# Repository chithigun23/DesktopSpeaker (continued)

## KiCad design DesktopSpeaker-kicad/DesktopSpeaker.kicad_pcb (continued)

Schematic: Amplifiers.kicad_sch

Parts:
C260, C267, C276, C278, C281, C289, C291, C294, C314: 100nF; C_0402_1005Metric_Pad0.74x0.62mm_HandSolder; MPN GRM155R71H104KE14D; LCSC C77020
C261, C262, C263, C264: 22uF 10V; C_0805_2012Metric_Pad1.18x1.45mm_HandSolder; MPN GRM21BZ71A226ME15L; LCSC C907991
C265: 2.2uF; C_0805_2012Metric_Pad1.18x1.45mm_HandSolder; MPN CL21B225KAFNNNE; LCSC C19110
C266: 47nF; C_0402_1005Metric_Pad0.74x0.62mm_HandSolder; MPN GRM155R71H473KE14D; LCSC C117757
C268: 6.8nF; C_0402_1005Metric_Pad0.74x0.62mm_HandSolder; MPN CL05B682KB5NNNC; LCSC C318580
C269: 47pF; C_0402_1005Metric_Pad0.74x0.62mm_HandSolder; MPN GRM1555C1H470JA01D; LCSC C76970
C270: 1uF; C_0805_2012Metric_Pad1.18x1.45mm_HandSolder; MPN CL21B105KBFNNNE; LCSC C28323
C271, C272, C273, C274, C277, C279, C290, C292: 22uF 25V; C_0805_2012Metric_Pad1.18x1.45mm_HandSolder; MPN CL21A226MAQNNNE; LCSC C45783
C275: 100uF 25V; CP_Elec_8x10; MPN EEHZA1E101XP; LCSC C264047
C280, C293: 4.7uF; C_0805_2012Metric_Pad1.18x1.45mm_HandSolder; MPN CL21A475KAQNNNE; LCSC C1779
C282, C283, C284, C295, C296, C297: 1uF; C_0402_1005Metric_Pad0.74x0.62mm_HandSolder; MPN CL05A105KO5NNNC; LCSC C29266
C285, C286, C287, C288, C298, C299, C300, C301: 0.47uF; C_0402_1005Metric_Pad0.74x0.62mm_HandSolder; MPN CGA0402X7R474K160GT; LCSC C22435970
C302, C303, C304, C305, C306, C307: 0.68uF 50V; C_0805_2012Metric_Pad1.18x1.45mm_HandSolder; MPN CL21B684KBFVPNE; LCSC C472832
J9, J10, J11: B2P-VH; JST_B2P_VH_1x02_P3.96mm_Vertical; MPN B2P-VH(LF)(SN); LCSC Part C160315
L200: 2.2uH; L_Coilcraft_XAL7070-XXX; MPN XAL7070-222MEC; LCSC C3911470
L201, L202, L203, L204, L205, L206: 22uH; L_Sunlord_MWSA1265S; MPN MWSA1265S-220MT; LCSC C7245133
R250: 499k; R_0402_1005Metric_Pad0.72x0.64mm_HandSolder; MPN RC0402FR-07499KL; LCSC C137971
R251: 56k; R_0402_1005Metric_Pad0.72x0.64mm_HandSolder; MPN RC0402FR-0756KL; LCSC C114756
R252: 301k; R_0402_1005Metric_Pad0.72x0.64mm_HandSolder; MPN RC0402FR-07301KL; LCSC C171693
R253: 150k; R_0402_1005Metric_Pad0.72x0.64mm_HandSolder; MPN RC0402FR-07150KL; LCSC C93947
R254: 82k; R_0402_1005Metric_Pad0.72x0.64mm_HandSolder; MPN AC0402FR-0782KL; LCSC C144735
R255, R259: 100k; R_0402_1005Metric_Pad0.72x0.64mm_HandSolder; MPN RC0402FR-07100KL; LCSC C60491
R256: 0R DNP; R_0402_1005Metric_Pad0.72x0.64mm_HandSolder; MPN RC0402FR-070RL; LCSC C106231; not fitted
R257, R258, R261: 1k; R_0402_1005Metric_Pad0.72x0.64mm_HandSolder; MPN RC0402FR-071KL; LCSC C106235
R262: 10k; R_0402_1005Metric_Pad0.72x0.64mm_HandSolder; MPN RC0402FR-0710KL; LCSC C60490
TP10: PVDD_AMP; TestPoint_Keystone_5015_Micro_Mini
TP20: AMP_FAULT_N; TestPoint_Keystone_5015_Micro_Mini
TP24: GND; TestPoint_Keystone_5010-5014_Multipurpose
U6, U7: TAS5825MRHBR; MPN TAS5825MRHBR; LCSC Part C471049
U25: TPS61088RHLR; MPN TPS61088RHLR; LCSC Part C87357

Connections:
/3V3_AUDIO: C280.1, C281.1, C293.1, C294.1, R262.1, U6.6 (DVDD), U7.6 (DVDD); also elsewhere on the board
/AMP_BOOST_EN: R255.1, U25.2 (EN); also elsewhere on the board
/AMP_FAULT_N: R262.2, TP20.1, U6.9 (GPIO0), U7.9 (GPIO0); also elsewhere on the board
/AMP_PDN: R257.1, R258.1, R259.1; also elsewhere on the board
/AUD_SCL: U6.16 (SCL), U7.16 (SCL); also elsewhere on the board
/AUD_SDA: U6.15 (SDA), U7.15 (SDA); also elsewhere on the board
/Amplifiers/PVDD_AMP: C270.1, C271.1, C272.1, C273.1, C274.1, C275.1 (+), C276.1, C277.1, C278.1, C279.1, C289.1, C290.1, C291.1, C292.1, C314.1, R250.1, TP10.1, U6.3, U6.4, U6.21, U6.22, U6.[3,4,21,22] (PVDD), U7.3, U7.4, U7.21, U7.22, U7.[3,4,21,22] (PVDD), U25.14, U25.15, U25.16, U25.[14-16] (VOUT)
/I2S_BCK: U6.13 (SCLK), U7.13 (SCLK); also elsewhere on the board
/I2S_LRCK: U6.12 (LRCLK), U7.12 (LRCLK); also elsewhere on the board
/I2S_SDATA: U6.14 (SDIN), U7.14 (SDIN); also elsewhere on the board
/SYS_RAW: C260.1, C261.1, C262.1, C263.1, C264.1, L200.1, U25.9 (VIN); also elsewhere on the board
GND: C260.2, C261.2, C262.2, C263.2, C264.2, C265.2, C266.2, C268.2, C269.2, C270.2, C271.2, C272.2, C273.2, C274.2, C275.2 (-), C276.2, C277.2, C278.2, C279.2, C280.2, C281.2, C282.2, C283.2, C284.2, C289.2, C290.2, C291.2, C292.2, C293.2, C294.2, C295.2, C296.2, C297.2, C302.2, C303.2, C304.2, C305.2, C306.2, C307.2, C314.2, R251.2, R253.2, R255.2, R256.2, R259.2, R261.1, TP24.1, U6.5, U6.8 (ADR), U6.20, U6.25, U6.26, U6.31, U6.32, U6.33, U6.[5,20,25,26,31,32,3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 (GND), U7.5, U7.20, U7.25, U7.26, U7.31, U7.32, U7.33, U7.[5,20,25,26,31,32,3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 (GND), U25.11, U25.12, U25.20 (AGND), U25.21, U25.[11,12,21] (PGND); also elsewhere on the board
unnamed: C268.1, R254.2
unnamed: C302.1, J9.1, L201.2
unnamed: C303.1, J9.2, L202.2
unnamed: C304.1, J10.1, L203.2
unnamed: C305.1, J10.2, L204.2
unnamed: C306.1, J11.1, L205.2
unnamed: C307.1, J11.2, L206.2
unnamed: C284.1, U6.19 (AVDD)
unnamed: C285.1, U6.1 (BST_A+)
unnamed: C286.2, U6.29 (BST_A-)
unnamed: C287.1, U6.24 (BST_B+)
unnamed: C288.2, U6.28 (BST_B-)
unnamed: C283.1, U6.18 (GVDD)
unnamed: C285.2, L201.1, U6.2 (OUT_A+)
unnamed: C286.1, L202.1, U6.30 (OUT_A-)
unnamed: C287.2, L203.1, U6.23 (OUT_B+)
unnamed: C288.1, L204.1, U6.27 (OUT_B-)
unnamed: C282.1, U6.7 (VR_DIG)
unnamed: R257.2, U6.17 (~PDN)
unnamed: R261.2, U7.8 (ADR)
unnamed: C297.1, U7.19 (AVDD)
unnamed: C298.1, U7.1 (BST_A+)
unnamed: C299.2, U7.29 (BST_A-)
unnamed: C300.1, U7.24 (BST_B+)
unnamed: C301.2, U7.28 (BST_B-)
unnamed: C296.1, U7.18 (GVDD)
unnamed: C298.2, C299.1, L205.1, U7.2 (OUT_A+), U7.30 (OUT_A-)
unnamed: C300.2, C301.1, L206.1, U7.23 (OUT_B+), U7.27 (OUT_B-)
unnamed: C295.1, U7.7 (VR_DIG)
unnamed: R258.2, U7.17 (~PDN)
unnamed: C267.1, U25.8 (BOOT)
unnamed: C269.1, R254.1, U25.18 (COMP)
unnamed: R250.2, R251.1, U25.17 (FB)
unnamed: R252.1, U25.3 (FSW)
unnamed: R253.1, U25.19 (ILIM)
unnamed: R256.1, U25.13 (MODE)
unnamed: C266.1, U25.10 (SS)
unnamed: C267.2, L200.2, R252.2, U25.4, U25.5, U25.6, U25.7, U25.[4-7] (SW)
unnamed: C265.1, U25.1 (VCC)

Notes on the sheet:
FRONT_L
FRONT_R
WOOFER
U7 PBTL pairing verified against SLASEH7F Fig. 159 / 10.2.5 (page 86 rendered): OUT_A+ (2) with OUT_A- (30) merged to L205; OUT_B+ (23) with OUT_B- (27) merged to L206; speaker between the two filtered nodes.
Firmware: write DAMP_PBTL (reg 0x02 bit 2) = 1 on U7 before it leaves Hi-Z; the PBTL mixer takes the left I2S frame, so the U7 DSP forms (L+R)/2. No cycle-by-cycle current limit in PBTL.
U25: VOUT = 1.204 V x (1 + 499k/56k) = 11.93 V (PFM: 12.0 V; OVP 12.7-13.6 V). FSW about 494 kHz (RFREQ 301k). ILIM 150k = 7.9 A typ, 6.6 A min in PFM (equation 3). L200 Isat 19.6 A.
COMP: R254 82k, C268 6.8nF, C269 47pF (equations 18-20, fc about 5 kHz, effective Co about 170 uF): calculated only, bench check required. MODE floating = PFM; R256 DNP 0R to GND = forced PWM.
TAS5825M addresses: U6 ADR tied directly to GND = 0x4C, U7 ADR 1k = 0x4D. AMP_PDN shared (1k each, 100k pull-down). GPIO0 = FAULTZ (open drain) wired-OR to AMP_FAULT_N, 10k pull-up to 3V3_AUDIO. GPIO1/2 not connected.
DVDD = 3V3_AUDIO. Bootstrap caps are 0.47uF (Table 66). Filter 22uH + 0.68uF per output. No MCLK pin: TAS5825M locks to SCLK. Speaker connectors: pin 1 +, pin 2 -.

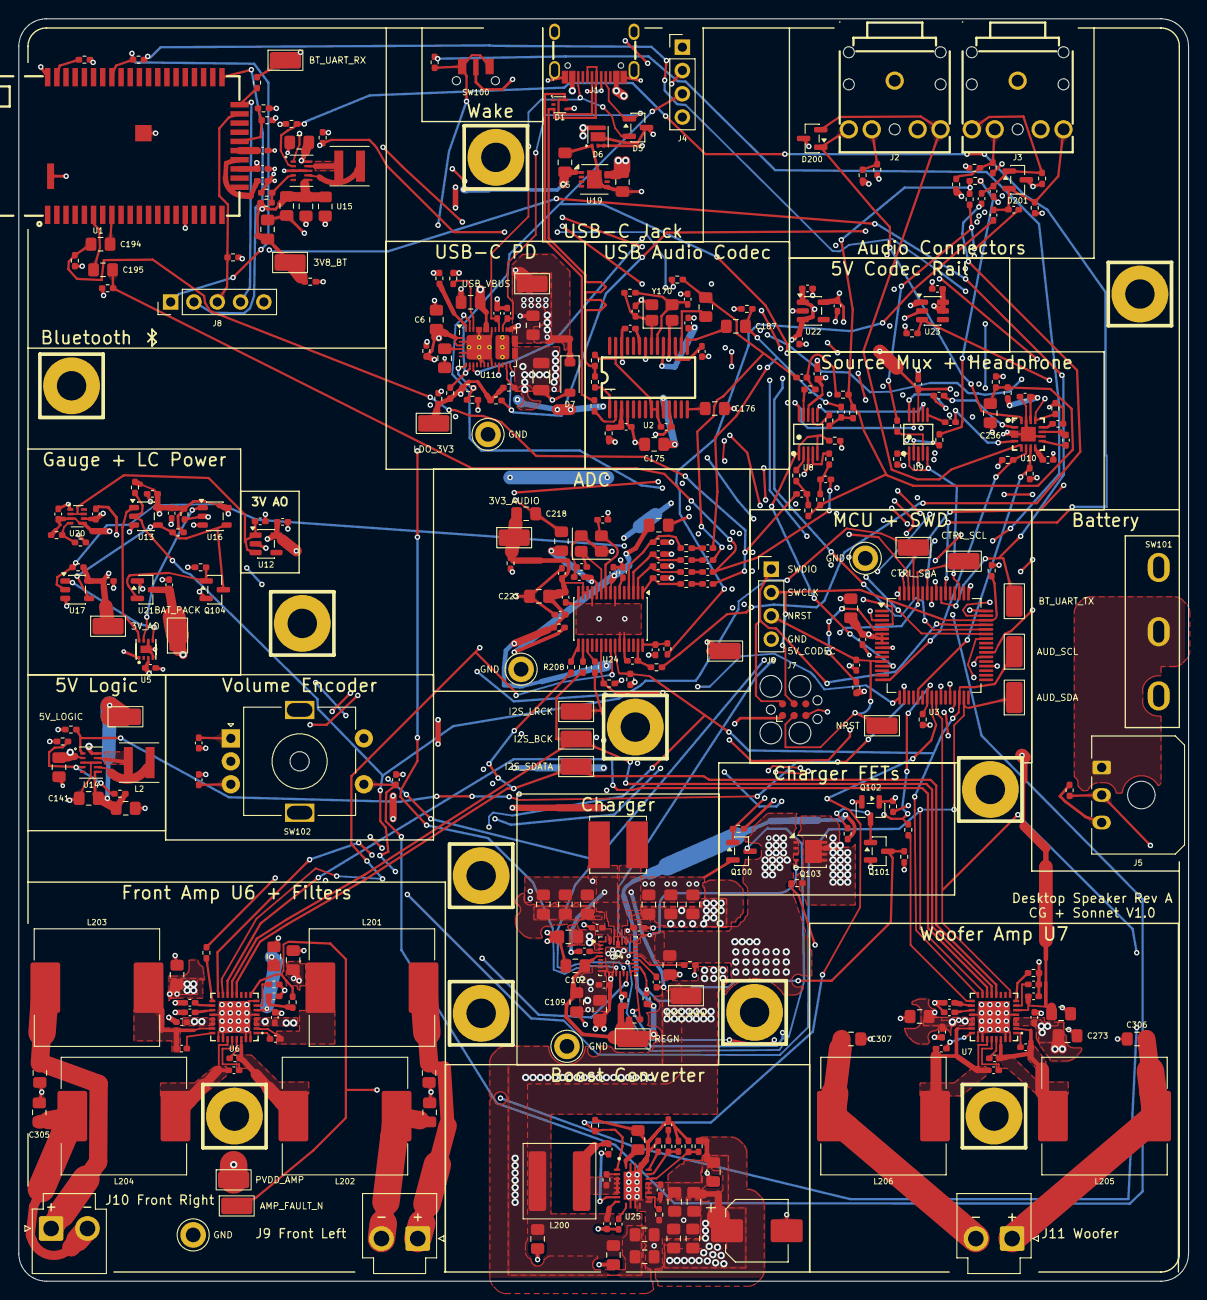
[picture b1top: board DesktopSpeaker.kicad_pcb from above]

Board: 4 copper layers, 127.5 x 137.6 mm, 360 parts (1 on the bottom side), 208 nets.

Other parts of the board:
H1, H2, H3, H4, H5, H6, H7, H8, H9: M3 PTH GND; MountingHole_3.2mm_M3_PTH_GND
HA1, HA2: M3 PTH GND; MountingHole_3.2mm_M3_PTH_GND
LOGO1: Orwellian Industries; Logo_Orwellian

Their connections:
GND: H1.1, H2.1, H3.1, H4.1, H5.1, H6.1, H7.1, H8.1, H9.1, HA1.1, HA2.1; also elsewhere on the board

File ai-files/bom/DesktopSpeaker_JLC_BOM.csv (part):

Comment,Designator,Footprint,LCSC Part #,MPN,Manufacturer,Qty
4.7uF X7R 50V,"C2,C5",C_0805_2012Metric_Pad1.18x1.45mm_HandSolder,C5159426,C2012X7R1H475KT0A0E,TDK,2
22uF 10V X7R,"C6,C104,C105,C106,C107,C140,C141,C142,C150,C152,C153,C154,C261,C262,C263,C264",C_0805_2012Metric_Pad1.18x1.45mm_HandSolder,C907991,GRM21BZ71A226ME15L,Murata,16
10uF / 50V,"C100,C101,C108,C111,C112",C_0805_2012Metric_Pad1.18x1.45mm_HandSolder,C440198,GRM21BR61H106KE43L,Murata,5
10uF,"C102,C109,C175,C176,C181,C190,C214,C216,C218,C223",C_0805_2012Metric_Pad1.18x1.45mm_HandSolder,C32635,CL21B106KPQNNNE,Samsung Electro-Mechanics,10
47nF / 50V,"C103,C110,C266",C_0402_1005Metric_Pad0.74x0.62mm_HandSolder,C117757,GRM155R71H473KE14D,Murata,3
100nF,"C120,C126,C130,C131,C132,C160,C162,C191,C213,C215,C217,C219,C237,C238,C246,C260,C267,C276,C278,C281,C289,C291,C294,C311,C312,C313,C314",C_0402_1005Metric_Pad0.74x0.62mm_HandSolder,C77020,GRM155R71H104KE14D,Murata,27
1uF,"C122,C123,C124,C125,C170,C171,C172,C173,C174,C192,C193,C212,C220,C221,C222,C224,C225,C230,C231,C232,C233,C234,C235,C239,C240,C245,C282,C283,C284,C295,C296,C297",C_0402_1005Metric_Pad0.74x0.62mm_HandSolder,C29266,CL05A105KO5NNNC,Samsung Electro-Mechanics,32
4.7uF,"C161,C186,C187,C194,C195,C236,C280,C293",C_0805_2012Metric_Pad1.18x1.45mm_HandSolder,C1779,CL21A475KAQNNNE,Samsung Electro-Mechanics,8
33pF,"C177,C178",C_0402_1005Metric_Pad0.74x0.62mm_HandSolder,C5137486,FCC0402N330J500AT,FOJAN,2
330pF C0G CC1 filter,"C182,C183",C_0402_1005Metric_Pad0.74x0.62mm_HandSolder,C76965,GRM1555C1H331JA01D,Murata,2
1uF X7R 50V,"C184,C270,C316",C_0805_2012Metric_Pad1.18x1.45mm_HandSolder,C28323,CL21B105KBFNNNE,Samsung Electro-Mechanics,3
2.2uF,"C200,C201,C202,C203,C204,C205,C241,C243,C244",C_0402_1005Metric_Pad0.74x0.62mm_HandSolder,C7464343,CL05A225KP5NNNC,Samsung Electro-Mechanics,9
10nF C0G,"C206,C207,C208,C209,C210,C211",C_0402_1005Metric_Pad0.74x0.62mm_HandSolder,C22400107,GRM1555C1H103JE01D,Murata,6
15pF C0G,"C226,C227",C_0402_1005Metric_Pad0.74x0.62mm_HandSolder,C76950,GRM1555C1H150JA01D,Murata,2
2.2uF,C265,C_0805_2012Metric_Pad1.18x1.45mm_HandSolder,C19110,CL21B225KAFNNNE,Samsung Electro-Mechanics,1
6.8nF,C268,C_0402_1005Metric_Pad0.74x0.62mm_HandSolder,C318580,CL05B682KB5NNNC,Samsung Electro-Mechanics,1
47pF,C269,C_0402_1005Metric_Pad0.74x0.62mm_HandSolder,C76970,GRM1555C1H470JA01D,Murata,1
22uF 25V,"C271,C272,C273,C274,C277,C279,C290,C292",C_0805_2012Metric_Pad1.18x1.45mm_HandSolder,C45783,CL21A226MAQNNNE,Samsung Electro-Mechanics,8
100uF 25V,C275,CP_Elec_8x10,C264047,EEHZA1E101XP,Panasonic,1
0.47uF,"C285,C286,C287,C288,C298,C299,C300,C301",C_0402_1005Metric_Pad0.74x0.62mm_HandSolder,C22435970,CGA0402X7R474K160GT,HRE,8
0.68uF 50V,"C302,C303,C304,C305,C306,C307",C_0805_2012Metric_Pad1.18x1.45mm_HandSolder,C472832,CL21B684KBFVPNE,Samsung Electro-Mechanics,6
10nF,"C308,C309,C310",C_0402_1005Metric_Pad0.74x0.62mm_HandSolder,C77019,GRM155R71H103KA88D,Murata,3
47uF 25V,C315,PD_C_1206,C403725,GRM31CR61E476ME44L,Murata,1
TPD2E2U06DRLR,D1,TPD2E2U06DRLR,C1972959,TPD2E2U06DRLR,Texas Instruments,1
ESDA25L,D5,ESDA25L,C95343,ESDA25L,STMicroelectronics,1
TVS2200DRVR,D6,TVS2200DRVR,C523793,TVS2200DRVR,Texas Instruments,1
1N5819HW,D7,PD_D_SOD123,C82544,1N5819HW-7-F,Diodes Incorporated,1
PESD5V0S2BT,"D200,D201",PESD5V0S2BT,C5380400,PESD5V0S2BT,DOWO,2
BLM15AG601SN1D,FB200,R_0402_1005Metric_Pad0.72x0.64mm_HandSolder,C76884,BLM15AG601SN1D,Murata,1
USB_C_Receptacle_USB2.0_16P,J1,TYPE-C-31-M-12,C165948,TYPE-C-31-M-12,Korean Hroparts,1
HEAD_OUT,"J2,J3",PJ-307,C2939173,PJ-307,HOOYA,2
I2C service,J4,PD_SERVICE_HDR,C124378,B-2100S04P-A110,Ckmtw,1
1S_PACK_3PIN,J5,Molex_Micro-Fit_3.0_43650-0300_1x03_P3.00mm_Horizontal,C503478,43650-0300,Molex,1
SWD,J6,PinHeader_1x04_P2.54mm_Vertical,C124378,B-2100S04P-A110,Ckmtw,1
BM83_PROG,J8,PinHeader_1x05_P2.54mm_Vertical,C54110162,XY-MTP254-1X5,XYECONN,1
B2P-VH,"J9,J10,J11",JST_B2P_VH_1x02_P3.96mm_Vertical,C160315,B2P-VH(LF)(SN),JST,3
2.2uH,L1,Bourns_SRN6045TA-2R2Y,C1332316,SRN6045TA-2R2Y,Bourns,1
0.47uH,"L2,L3",Coilcraft_XFL4015-471MEC,C18221164,XFL4015-471MEC,Coilcraft,2
2.2uH,L200,L_Coilcraft_XAL7070-XXX,C3911470,XAL7070-222MEC,Coilcraft,1
22uH,"L201,L202,L203,L204,L205,L206",L_Sunlord_MWSA1265S,C7245133,MWSA1265S-220MT,Sunlord,6
2N7002,"Q100,Q101,Q102,Q104",2N7002,C65189,"2N7002,215",Nexperia,4
CSD17579Q3A,Q103,CSD17579Q3A_DNH0008A,C97376,CSD17579Q3A,Texas Instruments,1
200k 1%,R10,R_0402_1005Metric_Pad0.72x0.64mm_HandSolder,C114763,RC0402FR-07200KL,Yageo,1
10k,"R11,R13,R14,R15,R18,R106,R182,R183,R242,R243,R244,R262",R_0402_1005Metric_Pad0.72x0.64mm_HandSolder,C60490,RC0402FR-0710KL,Yageo,12
100k,"R12,R16,R17,R103,R107,R109,R110,R111,R113,R125,R142,R152,R153,R154,R160,R175,R176,R180,R181,R184,R211,R212,R220,R221,R222,R223,R224,R225,R234,R235,R236,R237,R238,R239,R255,R259",R_0402_1005Metric_Pad0.72x0.64mm_HandSolder,C60491,RC0402FR-07100KL,Yageo,36
5.23k,R100,R_0402_1005Metric_Pad0.72x0.64mm_HandSolder,C25907,0402WGF5231TCE,UNI-ROYAL,1
30.1k,R101,R_0402_1005Metric_Pad0.72x0.64mm_HandSolder,C226982,AC0402FR-0730K1L,Yageo,1
4.7k,"R102,R120,R121",R_0402_1005Metric_Pad0.72x0.64mm_HandSolder,C105871,RC0402FR-074K7L,Yageo,3
180k,"R108,R124",R_0402_1005Metric_Pad0.72x0.64mm_HandSolder,C138046,RC0402FR-07180KL,Yageo,2
100,"R112,R200,R201,R202,R203,R204,R205",R_0402_1005Metric_Pad0.72x0.64mm_HandSolder,C106232,RC0402FR-07100RL,Yageo,7
47k,"R122,R232,R233",R_0402_1005Metric_Pad0.72x0.64mm_HandSolder,C93943,RC0402FR-0747KL,Yageo,3
1M,"R126,R127,R174,R241",R_0402_1005Metric_Pad0.72x0.64mm_HandSolder,C138033,RC0402FR-071ML,Yageo,4
78.7k 1%,R140,R_0402_1005Metric_Pad0.72x0.64mm_HandSolder,C163454,RC0402FR-0778K7L,Yageo,1
9.1k 1%,R141,R_0402_1005Metric_Pad0.72x0.64mm_HandSolder,C163450,RC0402FR-079K1L,Yageo,1
604k 1%,R150,R_0402_1005Metric_Pad0.72x0.64mm_HandSolder,C27013,0402WGF6043TCE,UNI-ROYAL,1
91k 1%,R151,R_0402_1005Metric_Pad0.72x0.64mm_HandSolder,C144733,AC0402FR-0791KL,Yageo,1
2.2,R170,R_0402_1005Metric_Pad0.72x0.64mm_HandSolder,C327251,RC0402FR-072R2L,Yageo,1
22,"R171,R172",R_0402_1005Metric_Pad0.72x0.64mm_HandSolder,C114765,RC0402FR-0722RL,Yageo,2
1.5k,R173,R_0402_1005Metric_Pad0.72x0.64mm_HandSolder,C114759,RC0402FR-071K5L,Yageo,1
1k,"R185,R186,R187,R226,R227,R228,R229,R230,R231,R240,R257,R258,R261",R_0402_1005Metric_Pad0.72x0.64mm_HandSolder,C106235,RC0402FR-071KL,Yageo,13
33,"R206,R207,R208",R_0402_1005Metric_Pad0.72x0.64mm_HandSolder,C138002,RC0402FR-0733RL,Yageo,3
2.2k,"R209,R210",R_0402_1005Metric_Pad0.72x0.64mm_HandSolder,C114762,RC0402FR-072K2L,Yageo,2
499k,R250,R_0402_1005Metric_Pad0.72x0.64mm_HandSolder,C137971,RC0402FR-07499KL,Yageo,1
56k,R251,R_0402_1005Metric_Pad0.72x0.64mm_HandSolder,C114756,RC0402FR-0756KL,Yageo,1
301k,R252,R_0402_1005Metric_Pad0.72x0.64mm_HandSolder,C171693,RC0402FR-07301KL,Yageo,1
150k,R253,R_0402_1005Metric_Pad0.72x0.64mm_HandSolder,C93947,RC0402FR-07150KL,Yageo,1
82k,R254,R_0402_1005Metric_Pad0.72x0.64mm_HandSolder,C144735,AC0402FR-0782KL,Yageo,1
WAKE_QON,SW100,TE_1977066-1_Tact_RA_SMD,C2972219,1977066-1,TE Connectivity,1
EC11E,SW102,RotaryEncoder_Alps_EC11E-Switch_Vertical_H20mm_MountingHoles,C370970,EC11E15244G1,Alps Alpine,1
BM83SM1-00TA,U1,BM83SM1-00TA,C6752723,BM83SM1-00TA,Microchip,1
PCM2902CDBR,U2,PCM2902CDBR,C2651869,PCM2902CDBR,Texas Instruments,1
STM32G071RBT6,U3,STM32G071RBT6,C432213,STM32G071RBT6,STMicroelectronics,1
BQ25792RQMR,U4,BQ25792RQMR,C2862876,BQ25792RQMR,Texas Instruments,1
MAX17048G+T10,U5,MAX17048G+T10,C2682616,MAX17048G+T10,Analog Devices,1
TAS5825MRHBR,"U6,U7",TAS5825MRHBR,C471049,TAS5825MRHBR,Texas Instruments,2
TS5A23157DGSR,"U8,U9",TS5A23157DGSR,C11133,TS5A23157DGSR,Texas Instruments,2
TPA6132A2RTER,U10,TPA6132A2RTER,C69901,TPA6132A2RTER,Texas Instruments,1
TPS25730DREFR,U11,TPS25730D,C22438973,TPS25730DREFR,Texas Instruments,1
TPS7A0230PDBVR,U12,TPS7A0230PDBVR,C3747031,TPS7A0230PDBVR,Texas Instruments,1
TS5A3167DBVR,"U13,U16,U17",TS5A3167DBVR,C128416,TS5A3167DBVR,Texas Instruments,3
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
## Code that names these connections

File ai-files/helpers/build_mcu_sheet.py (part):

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old = SYM.read_text()
props = old  # keep MPN/LCSC/manufacturer
LEFT = [  # (number, name, type)
    ('2', 'PC14', 'bidirectional'), ('3', 'PC15', 'bidirectional'),
    ('1', 'PB9', 'bidirectional'), ('7', 'PA0', 'bidirectional'), ('8', 'PA1', 'bidirectional'),
    ('9', 'PA2', 'bidirectional'), ('10', 'PA3', 'bidirectional'), ('11', 'PA4', 'bidirectional'),
    ('12', 'PA5', 'bidirectional'), ('13', 'PA6', 'bidirectional'), ('14', 'PA7', 'bidirectional'),
    ('15', 'PB0', 'bidirectional'), ('16', 'PB1', 'bidirectional'), ('17', 'PB2', 'bidirectional'),
    ('6', 'PF2-NRST', 'bidirectional')]
RIGHT = [
    ('24', 'PA13-SWDIO', 'bidirectional'), ('25', 'PA14-BOOT0', 'bidirectional'),
    ('31', 'PB7', 'bidirectional'), ('30', 'PB6', 'bidirectional'),
    ('23', 'PA12[PA10]', 'bidirectional'), ('22', 'PA11[PA9]', 'bidirectional'),
    ('21', 'PA10', 'bidirectional'), ('20', 'PC6', 'bidirectional'), ('19', 'PA9', 'bidirectional'),
    ('18', 'PA8', 'bidirectional'), ('29', 'PB5', 'bidirectional'), ('26', 'PA15', 'bidirectional'),
    ('27', 'PB3', 'bidirectional'), ('28', 'PB4', 'bidirectional'), ('32', 'PB8', 'bidirectional')]
eff = '(effects (font (size 1.27 1.27)))'
def pin(t, x, y, a, name, num, ln=2.54):
    return (f'(pin {t} line (at {f(x)} {f(y)} {a}) (length {ln}) (name "{name}" {eff}) (number "{num}" {eff}))')
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left_sig = ['PD_PLUG_EVENT', 'CHG_INT', 'PD_SINK_EN', 'GAUGE_ALRT_N']
for k, n in enumerate(left_sig):
    y = pyl(k); wire(LP, y, XL, y); hlabel(n, 'input', LP, y, 'left bottom')
for k in range(4, 14): nc(XL, pyl(k))           # PA1..PB2 reserved
# NRST (slot 14): wire to C162 + label
yn = pyl(14)
wire(XL, yn, 106.68, yn)
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             f'(property "LCSC" "C54110162" (at {f(jx)} {f(jy)} 0) (hide yes) (effects (font (size 1 1)))) '
             + ' '.join(f'(pin "{n}" (uuid "{U()}"))' for n in range(1, 6)) +
             f' (instances (project "DesktopSpeaker" (path "/{ROOT_UUID}/{SHEET_UUID}" (reference "J6") (unit 1)))))')
text('SWD: 1 SWDIO, 2 SWCLK, 3 NRST, 4 3V_AO (VTref), 5 GND\\nR160 holds PA14/BOOT0 low (nBOOT_SEL=1 ignores the pin)', jx - 20.32, 58.42)
# ---- right: buses and outputs
right_sig = [(2, 'CTRL_SDA', 'bidirectional'), (3, 'CTRL_SCL', 'bidirectional'), (4, 'PDCTRL_SDA', 'bidirectional'),
             (5, 'PDCTRL_SCL', 'bidirectional'), (6, 'CHG_SYS_ENABLE', 'output'), (7, 'CHG_ENABLE', 'output'),
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    out.append(l)
assert len(out) == len(lines) - 5
MX, MY, MW, MH = 320.04, 139.7, 50.8, 66.04
left_pins = [('3V_AO', 147.32), ('PD_PLUG_EVENT', 157.48), ('CHG_INT', 162.56), ('PD_SINK_EN', 167.64), ('GAUGE_ALRT_N', 195.58)]
right_pins = [('CTRL_SDA', 'bidirectional', 154.94), ('CTRL_SCL', 'bidirectional', 160.02), ('PDCTRL_SDA', 'bidirectional', 165.1),
              ('PDCTRL_SCL', 'bidirectional', 170.18), ('CHG_SYS_ENABLE', 'output', 177.8), ('CHG_ENABLE', 'output', 182.88),
              ('BT_FORCE_PWM', 'output', 187.96), ('BT_PWR_EN', 'output', 193.04), ('5V_LOGIC_EN', 'output', 198.12)]
sp = ' '.join(f'(pin "{n}" input (at {f(MX)} {f(y)} 180) (effects (font (size 1 1)) (justify left bottom)) (uuid "{U()}"))' for n, y in left_pins)
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
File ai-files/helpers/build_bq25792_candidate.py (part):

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def P(n): return pinpos[str(n)]

# Incoming VBUS; single-input topology ties VAC1/2 to VBUS, with ACDRV1/2 grounded.
vbus=P('[2-3]'); port('VBUS_PD',38,93,'input'); path((38,93),(70,93)); label('VBUS_PD',70,93)
path(vbus,(vbus[0],vbus[1]-5.08)); label('VBUS_PD',vbus[0],vbus[1]-5.08)
for n in ('8','9'):
    p=P(n); path(p,(p[0],p[1]-5.08)); label('VBUS_PD',p[0],p[1]-5.08)
for n in ('10','11'):
    p=P(n); path(p,(p[0]+6.35,p[1])); path((p[0]+6.35,p[1]),(p[0]+6.35,p[1]+5.08)); gnd(p[0]+6.35,p[1]+5.08)
nc(*P('1')) # STAT unused; charge state is available on I2C/INT.
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    passive(ref,x,99,value=val,footprint='DesktopSpeaker:PD_C_1210')
    for p in allof(obj_by_ref[ref],'property'):
        if p[1] in ('MPN','LCSC Part','LCSC','Manufacturer','Datasheet'): p[2]=''
    path((x,95.19),(x,88.9)); label('VBUS_PD',x,88.9); path((x,102.81),(x,110)); gnd(x,110)
new_cap('C111','10uF / 50V',140,99,template='C103',footprint='DesktopSpeaker:PD_C_1210')
path((140,95.19),(140,88.9)); label('VBUS_PD',140,88.9); path((140,102.81),(140,110)); gnd(140,110)
new_cap('C113','0.1uF / 50V',165,99,footprint='DesktopSpeaker:PD_C_0402')
path((165,95.19),(165,88.9)); label('VBUS_PD',165,88.9); path((165,102.81),(165,110)); gnd(165,110)
pmid=P('29')
for ref,x in [('C101',270),('C108',292)]:
    passive(ref,x,99,value='10uF / 35V',footprint='DesktopSpeaker:PD_C_1210')
    for p in allof(obj_by_ref[ref],'property'):
        if p[1] in ('MPN','LCSC Part','LCSC','Manufacturer','Datasheet'): p[2]=''
    path((x,95.19),(x,89.0)); label('PMID',x,89.0); path((x,102.81),(x,110)); gnd(x,110)
new_cap('C112','10uF / 35V',314,99,template='C103',footprint='DesktopSpeaker:PD_C_1210')
path((314,95.19),(314,89.0)); label('PMID',314,89.0); path((314,102.81),(314,110)); gnd(314,110)
new_cap('C114','0.1uF / 50V',336,99,footprint='DesktopSpeaker:PD_C_0402')
new_cap('C115','0.1uF / 50V',350,99,footprint='DesktopSpeaker:PD_C_0402')  # SYS bypass at U4 pin 25
path((336,95.19),(336,89.0)); label('PMID',336,89.0); path((336,102.81),(336,110)); gnd(336,110)
path(pmid,(260,pmid[1])); label('PMID',260,pmid[1])

# REGN decoupling and 2-rail bootstraps (C103 retained, C110 added).
regn=P('5')
for ref,x in [('C102',358),('C109',380)]:
    passive(ref,x,99,value='10uF / 10V'); path((x,95.19),(x,89.0)); label('REGN',x,89.0); path((x,102.81),(x,110)); gnd(x,110)
path(regn,(304,regn[1])); label('REGN',304,regn[1])
for n,cap,x in [('4','C103',278),('19','C110',302)]:
    p=P(n); sw=P('28' if n=='4' else '26')
    passive(cap,x,178,value='47nF / 50V',footprint='DesktopSpeaker:PD_C_0603')
    # Discrete local labels avoid crossing the bridge pins/inductor node.
    path(p,(p[0]+3.81,p[1])); label('BTST1' if n=='4' else 'BTST2',p[0]+3.81,p[1])
    path(sw,(sw[0]+3.81,sw[1])); label('SW1' if n=='4' else 'SW2',sw[0]+3.81,sw[1])
    ctop=(x,174.19); cbot=(x,181.81)
    path(ctop,(x,171)); label('BTST1' if n=='4' else 'BTST2',x,171)
    path(cbot,(x,185)); label('SW1' if n=='4' else 'SW2',x,185)

# Two switching nodes and the 2.2uH 750kHz power inductor.
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
# SYS regulated output rail and decoupling.
sys=P('25'); port('SYS_RAW',390,sys[1],'output','right')
path(sys,(390,sys[1])); label('SYS_RAW',365,sys[1])
for ref,x in [('C104',330),('C105',350),('C107',370)]:
    passive(ref,x,178,value='22uF / 10V'); path((x,174.19),(x,sys[1])); path((x,181.81),(x,188.0)); gnd(x,188.0)
    if ref!='C104': junction(x,sys[1])

# Charger ground and battery-internal rail decoupling. BAT and BAT_PACK remain isolated pending Q103.
g=P('27'); path(g,(g[0],g[1]+5.08)); gnd(g[0],g[1]+5.08)
bat=P('[22-23]'); path(bat,(bat[0]+5.08,bat[1])); label('BAT_INT',bat[0]+5.08,bat[1])
passive('C106',325,211,value='22uF / 10V'); path((325,207.19),(325,201)); label('BAT_INT',325,201); path((325,214.81),(325,221.16)); gnd(325,221.16)
instance_from_template('J5',375,245,value='1S_PACK_3PIN',footprint='DesktopSpeaker:JST_B3P_VH_1x03_P3.96mm_Vertical')
# Pin endpoints of Conn_01x03 at angle 0: pins 1,2,3 are vertically ordered.
j1=(369.92,242.46); j2=(369.92,245.0); j3=(369.92,247.54)
instance_from_template('SW101',360,242.46,value='BAT_DISCONNECT')
path(j1,(365.08,242.46)); label('PACK_RAW',365.08,242.46)
path((354.92,242.46),(320,242.46)); label('BAT_PACK',320,242.46)
path(j2,(365,j2[1])); label('TS_SENSE',365,j2[1])
path(j3,(365,j3[1]),(365,262)); gnd(365,262)
port('BAT_PACK',390,242.46,'bidirectional','right'); path((320,242.46),(390,242.46))

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for key,val in [('MPN','CSD17579Q3A'),('LCSC Part','C97376'),('Manufacturer','Texas Instruments'),('Datasheet','https://www.ti.com/lit/ds/symlink/csd17579q3a.pdf')]:
    sch[-1].insert(next(i for i,v in enumerate(sch[-1]) if k(v)=='pin'),[S('property'),key,val,at(330,235),eff(hide=True)])
q103_s=(332.54,240.08); q103_d=(332.54,229.92); q103_g=(324.92,235)
path(q103_s,(320,240.08),(320,242.46)); label('BAT_INT',320,240.08)
path(q103_d,(340,229.92),(340,225)); label('BAT_PACK',340,225)
path(q103_g,(315,235)); label('SDRV',315,235)

# BATP sense is isolated from the external battery terminal by the TI 100-ohm series resistor.
batp=P('18'); path(batp,(batp[0]+5.08,batp[1])); label('BATP_SENSE',batp[0]+5.08,batp[1])
passive('R112',348,212,angle=90,value='100R'); path((344.19,212),(335,212)); label('BAT_PACK',335,212)
path((351.81,212),(356,212)); label('BATP_SENSE',356,212)

# 1S PROG setup; R102 repurposed from the retired old-charger ILIM resistor.
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path(prog,(prog[0]-14,prog[1]),(150,prog[1]),(150,210.19),(164,210.19)); path((164,217.81),(164,225)); gnd(164,225)

# TS network preserves the pack NTC port plus provisional fixed bias resistors.
ts=P('16'); path(ts,(ts[0]-5.08,ts[1])); label('TS_SENSE',ts[0]-5.08,ts[1])
passive('R100',188,199,value='5.23k'); path((188,195.19),(188,184)); label('REGN',188,184); path((188,202.81),(188,208)); label('TS_SENSE',188,208)
passive('R101',212,236,value='30.1k'); path((212,232.19),(212,227)); label('TS_SENSE',212,227); path((212,239.81),(212,246)); gnd(212,246)

# Default-off SYS converter gate: Q101 clamps ILIM_HIZ low until Q102 is enabled.
# REGN-fed divider is deliberately about 0.8–1.1A across 4.6–5.2V, not a fixed-6V assumption.
ilim=P('17'); path(ilim,(186,ilim[1])); label('ILIM_HIZ',186,ilim[1])
passive('R108',173,180,value='180k'); passive('R109',190,197,value='100k')
path((173,176.19),(173,168),(185,168)); label('REGN',185,168)
path((173,183.81),(173,ilim[1]),(186,ilim[1])); path((190,193.19),(190,ilim[1]),(173,ilim[1])); junction(173,ilim[1]); path((190,200.81),(190,207)); gnd(190,207)
make_generic('2N7002:2N7002','Q101','2N7002',222,215,'DesktopSpeaker:2N7002')
# Q101 drain to ILIM_HIZ, source GND, gate held at REGN through R110 (default clamp ON).
q1gate=(216.92,215); q1drain=(224.54,209.92); q1source=(224.54,220.08)
path(q1drain,(230,209.92),(230,ilim[1]),(186,ilim[1])); path(q1source,(224.54,226)); gnd(224.54,226)
passive('R110',205,203,value='100k'); path((205,199.19),(205,168),(185,168)); label('REGN',185,168); path((205,206.81),(205,215),(216.92,215)); junction(205,215)
make_generic('2N7002:2N7002','Q102','2N7002',257,233,'DesktopSpeaker:2N7002')
q2gate=(251.92,233); q2drain=(259.54,227.92); q2source=(259.54,238.08)
port('CHG_SYS_ENABLE',38,233,'input'); path((38,233),(80,233),q2gate)
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
# CE remains a separate charge-only enable, pulled high at reset and sunk by the preserved Q100.
ce=P('13');
port('CHG_ENABLE',38,230,'input'); path((38,230),(135,230),(167,230)); label('CHG_ENABLE',135,230)
make_generic('2N7002:2N7002','Q100','2N7002',172,244,'DesktopSpeaker:2N7002')
qg=(166.92,244); qd=(174.54,238.92); qs=(174.54,249.08)
path(ce,(ce[0]-10,ce[1]),(ce[0]-10,238.92),(174.54,238.92)); path(qd,(174.54,238.92)); path(qs,(174.54,255)); gnd(174.54,255)
passive('R103',192,228,value='10k'); path((192,224.19),(192,214),(205,214)); label('REGN',205,214); path((192,231.81),(192,238.92),(174.54,238.92)); junction(174.54,238.92)
path((167,230),(qg[0],230),qg)
passive('R107',146,247,value='100k'); path((146,243.19),(146,230)); junction(146,230); path((146,250.81),(146,257)); gnd(146,257)

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    p=P(pn); port(n,38,py,'bidirectional' if 'SCL' in n or 'SDA' in n else 'input'); path((38,py),(185,py),(185,p[1]),p)
for n,pn in [('CHG_INT','21')]:
    p=P(pn); path(p,(p[0]-7.62,p[1])); label(n,p[0]-7.62,p[1])
port('CHG_INT',390,209,'output','right'); path((382.38,209),(390,209)); label('CHG_INT',382.38,209)
vio=(175,195); port('CHG_VIO_3V0',*vio,'input'); passive('R106',190,222,value='10k')
path((190,218.19),(190,195),(175,195)); path((190,225.81),(190,233)); label('CHG_INT',190,233)

# Keep the QON button, separate mechanical pack switch, and open notes reviewable.
qon=P('12');
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# ---- PMID rail and REGN rail -----------------------------------------------------
PY=83.82
pm=P4('29'); pcx=[264.16,284.48,304.8,325.12]
path(pm,(pm[0],PY)); hrail(PY,[pm[0]]+pcx); label('PMID',251.46,PY)
for x in pcx[:-1]: junction(x,PY)
for ref,x in zip(('C101','C108','C112','C114'),pcx):
    place(ref,x,PY+3.81); gnd(*pin(ref,'2'))
rg=P4('5'); rcx=[264.16,284.48]
path(rg,(rg[0],RY)); hrail(RY,[rg[0]]+rcx); label('REGN',254.0,RY); junction(rcx[0],RY)
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
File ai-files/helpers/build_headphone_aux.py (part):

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
# =========================================================== layout (local coordinates)
X0 = -165.1                      # left ports
# ---- six input networks: port - 1uF - node(100k to VMID_HP) - 1k - jog - mux pin
U8c = (-50.8, 38.1); U9c = (12.7, -12.7); U10c = (88.9, -17.78)
rows = [('USB_AUDIO_L', 66.04, 45.72, -91.44), ('USB_AUDIO_R', 53.34, 43.18, -99.06),
        ('BT_AUDIO_L', 35.56, 40.64, -106.68), ('BT_AUDIO_R', 22.86, 38.1, -91.44),
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    wire((X0, y), (-157.48, y))
    cap(f'C{230+k}', '1uF', C1U, (-153.67, y), True)
    wire((-149.86, y), (-138.43, y)); junc((-142.24, y))
    vres(f'R{220+k}', '100k', R100K, (-142.24, y)); label('VMID_HP', (-142.24, y - 7.62))
    res(f'R{226+k}', '1k', R1K, (-134.62, y), True)
    pts = [(-130.81, y)]
    if abs(py - y) > 1e-6: pts += [(xj, y), (xj, py)]
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           [('[2,3,10,17]', U())] + [(n, u) for n, u in oldpins('U10') if n in ('4', '5', '6', '7', '8', '9', '11', '12', '13', '14', '15', '16')])
# series input caps from the mux commons
cy1 = uy + 12.7; cy2 = uy + 2.54
wire((U9c[0] + 17.78, U9c[1] + 7.62), (55.88, cy1)); label('HP_L', (40.64, cy1))
cap('C239', '1uF', C1U, (59.69, cy1), True); wire((63.5, cy1), (ux - 17.78, cy1))
wire((U9c[0] + 17.78, U9c[1] + 5.08), (36.83, U9c[1] + 5.08), (36.83, cy2), (55.88, cy2)); label('HP_R', (45.72, cy2))
cap('C240', '1uF', C1U, (59.69, cy2), True); wire((63.5, cy2), (ux - 17.78, cy2))
# control pins EN, G0, G1 (ports with pull-downs at the left of the sheet; matching labels here)
for dy, nm in ((-10.16, 'HP_EN'), (-12.7, 'HP_G0'), (-15.24, 'HP_G1')):
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transplant('J2', J2c, 180, None, (J2c[0] + 13.97, J2c[1] + 1.27), (J2c[0] + 13.97, J2c[1] - 1.27), None, 'left')
jx = J2c[0] - 7.62
tipy, ringy, sley = J2c[1] + 6.35, J2c[1] - 1.27, J2c[1] - 3.81
wire((rx, uy + 12.7), (jx, tipy)); label('HP_OUTL', (116.84, tipy))
wire((rx, uy + 5.08), (jx, ringy)); label('HP_OUTR', (116.84, ringy))
wire((rx, uy + 2.54), (jx, sley)); junc((139.7, sley)); wire((139.7, sley), (139.7, sley - 2.54)); gnd((139.7, sley - 2.54))
wire((jx, J2c[1] + 3.81), (jx - 3.81, J2c[1] + 3.81)); label('HP_TIPSW', (jx - 3.81, J2c[1] + 3.81), 'right bottom')
nc((jx, J2c[1] + 1.27))
# D200 across tip and ring
D200c = (147.32, -40.64)
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esd('D200', D200c, 'HP_OUTL', 'HP_OUTR')
# HP_DET: switched tip, 100k pull-up to 3V3_AUDIO, 1k series to the MCU
hy = -17.78
wire((172.72, hy), (177.8, hy)); label('HP_TIPSW', (172.72, hy), 'right bottom'); junc((177.8, hy))
vres('R239', '100k', R100K, (177.8, hy + 7.62)); label('3V3_AUDIO', (177.8, hy + 7.62))
res('R240', '1k', R1K, (190.5, hy), True); wire((177.8, hy), (186.69, hy)); wire((194.31, hy), (198.12, hy))
hlabel('HP_DET', 'output', (198.12, hy), 0)
# ---- J3 AUX_IN (mirrored: pins on the right, tip on top)
J3c = (139.7, -67.31)
transplant('J3', J3c, 0, 'x', (J3c[0] - 8.89, J3c[1] + 11.43), (J3c[0] - 8.89, J3c[1] + 9.53), None, 'left')
jx3 = J3c[0] + 7.62
t3, r3, s3 = J3c[1] + 6.35, J3c[1] - 1.27, J3c[1] - 3.81
wire((jx3, t3), (198.12, t3)); hlabel('AUX_L', 'output', (198.12, t3), 0)
wire((jx3, r3), (198.12, r3)); hlabel('AUX_R', 'output', (198.12, r3), 0)
wire((jx3, s3), (jx3 + 2.54, s3)); gnd((jx3 + 2.54, s3))
wire((jx3, J3c[1] + 3.81), (jx3 + 3.81, J3c[1] + 3.81)); label('AUX_TIPSW', (jx3 + 3.81, J3c[1] + 3.81))
nc((jx3, J3c[1] + 1.27))
# D201 and bleeds
esd('D201', (116.84, -76.2), 'AUX_L', 'AUX_R')
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    label(nm, (x, -66.04), 'left bottom'); wire((x, -66.04), (x, -67.31)); vres(ref, '10k', R10K, (x, -67.31)); gnd((x, -74.93))
# AUX_DET: switched tip, 1M to 3V_AO, 100 nF filter, 10k series to the MCU
ay = -83.82
wire((172.72, ay), (177.8, ay)); label('AUX_TIPSW', (172.72, ay), 'right bottom'); junc((177.8, ay))
vres('R241', '1M', R1M, (177.8, ay + 7.62)); wire((177.8, ay + 7.62), (172.72, ay + 7.62)); hlabel('3V_AO', 'input', (172.72, ay + 7.62), 180)
junc((181.61, ay)); vcap('C246', '100nF', C100N, (181.61, ay))
wire((177.8, ay), (186.69, ay)); res('R242', '10k', R10K, (190.5, ay), True); wire((194.31, ay), (198.12, ay))
hlabel('AUX_DET', 'output', (198.12, ay), 0)
# ---- VMID_HP: 47k / 47k from 3V3_AUDIO with 4.7 uF
dx = -160.02
hlabel('3V3_AUDIO', 'input', (X0, -17.78), 180); wire((X0, -17.78), (dx, -17.78), (dx, -20.32))
res('R232', '47k', R47K, (dx, -24.13)); junc((dx, -27.94))
res('R233', '47k', R47K, (dx, -31.75)); gnd((dx, -35.56))
wire((dx, -27.94), (-148.59, -27.94)); label('VMID_HP', (-157.48, -27.94))
vcap('C236', '4.7uF', C4U7, (-148.59, -27.94))
# ---- control ports with 100k pull-downs (default low: USB source, amp off, -6 dB)
for k, nm in enumerate(('HP_SEL_A', 'HP_SEL_B', 'HP_EN', 'HP_G0', 'HP_G1')):
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    return s.replace(a, b)
# replace the old AUX note
m = re.search(r'\(text "AUX_L/AUX_R come from the later Headphone_Aux sheet[^\n]*\n', rt); assert m
rt = rt[:m.start()] + (f'(text "AUX_L/AUX_R leave the Headphone_Aux sheet (J3 AUX_IN) and join the Source_Select_ADC inputs by label. USB_AUDIO and BT_AUDIO nets fan out to both sheets. Speaker mute on headphone insertion is firmware only (HP_DET)." '
                       f'(at 20.32 86.36 0) (effects (font (size 1 1)) (justify left bottom)) (uuid "{U()}"))\n') + rt[m.end():]
# MCU sheet block: grow upward for 5 outputs, add 2 inputs
mcu_i = rt.index('(property "Sheet name" "MCU"'); sh_a = rt.rfind('(sheet (at', 0, mcu_i)
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
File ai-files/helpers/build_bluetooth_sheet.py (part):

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yL = SL(0)
wire((-25.4, yL), (-46.99, yL)); wire((-54.61, yL), (LP, yL))
res('R185', '1k', 'RC0603FR-071KL', 'C22548', (-50.8, yL), True)
label('BT_RST_M', (-43.18, yL), 'left bottom'); hlabel('BT_RST_N', 'input', (LP, yL), 'left bottom')
# UART RXD: 10k series (back-power limit)
yL = SL(5)
wire((-25.4, yL), (-46.99, yL)); wire((-54.61, yL), (LP, yL))
res('R182', '10k', 'RC0603FR-0710KL', 'C98220', (-50.8, yL), True)
label('BT_RXD_M', (-43.18, yL), 'left bottom'); hlabel('BT_UART_TX', 'input', (LP, yL), 'left bottom')
# P3_4 / SYS_CFG: floating = application mode; header only
yL = SL(8)
wire((-25.4, yL), (-33.02, yL)); label('BT_SYS_CFG', (-33.02, yL), 'right bottom')
# MFB: 10k series + 100k pull-down on module side
yL = SL(11)
wire((-25.4, yL), (-46.99, yL)); wire((-54.61, yL), (LP, yL))
res('R183', '10k', 'RC0603FR-0710KL', 'C98220', (-50.8, yL), True)
hlabel('BT_MFB', 'input', (LP, yL), 'left bottom')
junc((-38.1, yL)); res('R184', '100k', 'RC0603FR-07100KL', 'C14675', (-38.1, yL - 3.81), False); gnd((-38.1, yL - 7.62))
# ground (native stack 16/50/56/57)
yg = SL(26)
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notes = [
 'BM83SM1-00TA (DS70005402D). BAT_IN 3.2-4.2 V from 3V8_BT (U15); SYS_PWR/VDD_IO are outputs (decoupling only, do not load or feed). ADAP_IN unused (internal charger/USB DFU not used).',
 'Host mode UART from the MCU: P8_6 RXD / P8_5 TXD, P0_0 = UART_TX_IND (wakes the MCU). MFB (PWR) = power-on/wake key, RST_N = reset (active low, internal pull-up). Config Tool must set Host mode, P0_0 as TX_IND.',
 'Back-power: MCU lines pass 10k/1k series resistors; firmware must drive PA2/PB3 low (PB4 open-drain/hi-Z) and disable BT_PWR_EN only after the module power-off ACK. Module outputs are 3.0-3.6 V into 5 V tolerant MCU pins.',
 'Audio: single-ended DAC out (AOHPL/AOHPR) AC-coupled, 4.7 uF + 100k bleed, 0.74 Vrms full scale; AOHPM (capless sense) unused. Ports feed the later source-select sheet.',
 'Antenna: integrated PCB antenna, no external RF parts. Keep the antenna end of the module off the board (no copper/components/keep-out) and metal 15 mm clear; see ai-files/reports/bluetooth-notes.md.',
 'J8 programming/test (isUpdate/Config Tool): 1 RST_N, 2 P3_4 SYS_CFG (low at reset = test mode), 3 UART_RXD (adapter TX), 4 UART_TXD (adapter RX), 5 GND. 3V8_BT must be enabled first.',
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assert 'BT_UART_TX' not in m
def swap_pins(text):
    a = '(pin bidirectional line (at -25.4 5.08 0) (length 2.54) (name "PA2"'
    b = '(pin bidirectional line (at 25.4 -17.78 180) (length 2.54) (name "PB8"'
    assert text.count(a) == 1 and text.count(b) == 1
    text = text.replace(a, '(pin bidirectional line (at 25.4 -17.78 180) (length 2.54) (name "PA2"')
    text = text.replace(b, '(pin bidirectional line (at -25.4 5.08 0) (length 2.54) (name "PB8"')
    return text
m = swap_pins(m)
sm = SYM_MCU.read_text(); SYM_MCU.write_text(swap_pins(sm))
# remove NC flags: PB8 (left slot5, y95.25) and PA3 (97.79) on the left; PB3/PB4/PA2 on the right (113.03, 115.57, 118.11)
for x, y in ((114.3, 95.25), (114.3, 97.79), (165.1, 113.03), (165.1, 115.57), (165.1, 118.11)):
    m, n = re.subn(rf'\(no_connect \(at {f(x)} {f(y)}\) \(uuid "[0-9a-f-]+"\)\)\n', '', m)
    assert n == 1, (x, y)
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
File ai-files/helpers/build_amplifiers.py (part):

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    pin('input', -E, 25.4, 0, 'SCLK', '13', e=eff10), pin('input', -E, 22.86, 0, 'LRCLK', '12', e=eff10), pin('input', -E, 20.32, 0, 'SDIN', '14', e=eff10),
    pin('bidirectional', -E, 12.7, 0, 'SDA', '15', e=eff10), pin('input', -E, 10.16, 0, 'SCL', '16', e=eff10),
    pin('input', -E, 2.54, 0, '~{PDN}', '17', e=eff10), pin('passive', -E, -5.08, 0, 'ADR', '8', e=eff10),
    pin('open_collector', -E, -12.7, 0, 'GPIO0', '9', e=eff10), pin('bidirectional', -E, -15.24, 0, 'GPIO1', '10', e=eff10),
    pin('bidirectional', -E, -17.78, 0, 'GPIO2', '11', e=eff10),
    pin('power_in', -7.62, 33.02, 270, 'DVDD', '6', e=eff10), pin('power_in', 7.62, 33.02, 270, 'PVDD', '[3,4,21,22]', e=eff10),
    pin('power_out', -17.78, -35.56, 90, 'VR_DIG', '7', 7.62, eff10), pin('power_out', -10.16, -35.56, 90, 'GVDD', '18', 7.62, eff10),
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# input rail SYS_RAW: VIN up to the rail, 0.1 uF + 4 x 22 uF, L200 from the rail to SW
RY_ = 30.48
wire((-7.62, 20.32), (-7.62, RY_), (-88.9, RY_))
hlabel('SYS_RAW', 'input', (-88.9, RY_), 180)
junc((-78.74, RY_))
for x in (-17.78, -30.48, -43.18, -55.88, -68.58): junc((x, RY_))
cap('C260', '100nF', C100N, (-17.78, RY_ - 3.81)); gnd((-17.78, RY_ - 7.62))
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wire((-15.24, -7.62), (-30.48, -7.62)); vres('R252', '301k', R301K, (-30.48, -7.62)); wire((-30.48, -15.24), (-30.48, -22.86))
wire((-15.24, -15.24), (-17.78, -15.24)); rcap('C267', '100nF', C100N, (-17.78, -15.24), tl=True)
# EN (AMP_BOOST_EN port) with pull-down
wire((-15.24, 5.08), (-33.02, 5.08)); junc((-22.86, 5.08)); hlabel('AMP_BOOST_EN', 'input', (-33.02, 5.08), 180)
vres('R255', '100k', R100K, (-22.86, 5.08)); gnd((-22.86, -2.54))
# MODE: floating = PFM; DNP 0R to GND = forced PWM option
wire((-15.24, -30.48), (-27.94, -30.48)); vres('R256', '0R DNP', R0, (-27.94, -30.48), dnp=True); gnd((-27.94, -38.1))
# VCC 2.2 uF
wire((2.54, 20.32), (2.54, 27.94), (15.24, 27.94)); vcap('C265', '2.2uF', C2U2, (15.24, 27.94))
# VOUT rail: feedback divider, output capacitors, PVDD_AMP
wire((15.24, 15.24), (114.3, 15.24)); label('PVDD_AMP', (114.3, 15.24))
junc((17.78, 15.24))
vres('R250', '499k', R499K, (17.78, 15.24)); wire((15.24, 7.62), (17.78, 7.62)); junc((17.78, 7.62))
vres('R251', '56k', R56K, (17.78, 7.62)); gnd((17.78, 0))
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    wire((X(-E - 7.62), Y(2.54)), (X(-35.56), Y(2.54)))
    if first:
        wire((X(-35.56), Y(2.54)), (X(-48.26), Y(2.54))); junc((X(-43.18), Y(2.54)))
        hlabel('AMP_PDN', 'input', (X(-48.26), Y(2.54)), 180)
        vres(rD, '100k', R100K, (X(-43.18), Y(2.54))); gnd((X(-43.18), Y(-5.08)))
    else:
        label('AMP_PDN', (X(-35.56), Y(2.54)), 'right bottom')
    # ADR strap
    res(rB, adr_val, adr_part, (X(-E - 3.81), Y(-5.08)), True); gnd((X(-E - 7.62), Y(-5.08)))
    # GPIO0 FAULT (open drain, wired-OR), GPIO1/2 unused
    wire((X(-E), Y(-12.7)), (X(-30.48), Y(-12.7))); label('AMP_FAULT_N', (X(-30.48), Y(-12.7)), 'right bottom')
    nc((X(-E), Y(-15.24))); nc((X(-E), Y(-17.78)))
    # --- DVDD (3V3_AUDIO) and PVDD (PVDD_AMP) rails
    wire((X(-7.62), Y(33.02)), (X(-7.62), Y(45.72)), (X(-40.64), Y(45.72)))
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    junc((X(-17.78), Y(45.72))); junc((X(-30.48), Y(45.72)))
    c1, c2, c3, c4, c5, c6 = caprefs[:6]
    vcap(c1, '4.7uF', C4U7, (X(-17.78), Y(45.72))); vcap(c2, '100nF', C100N, (X(-30.48), Y(45.72)))
    wire((X(7.62), Y(33.02)), (X(7.62), Y(45.72)), (X(76.2), Y(45.72))); label('PVDD_AMP', (X(76.2), Y(45.72)))
    for dx, nm, v, part in ((17.78, c3, '100nF', C100N), (33.02, c4, '22uF 25V', C22_25), (48.26, c5, '100nF', C100N), (63.5, c6, '22uF 25V', C22_25)):
        junc((X(dx), Y(45.72))); vcap(nm, v, part, (X(dx), Y(45.72)))
    # --- internal regulator capacitors and ground stack
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fx = CX + 129.54
x_, y_ = fx, U7c[1] - 17.78
label('3V3_AUDIO', (x_, y_)); vres('R262', '10k', R10K, (x_, y_))
wire((fx, U7c[1] - 25.4), (fx, U7c[1] - 27.94), (fx + 7.62, U7c[1] - 27.94)); hlabel('AMP_FAULT_N', 'output', (fx + 7.62, U7c[1] - 27.94), 0)
# notes
NX, NY = -99.06, -60.96
notes = [
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    'Firmware: write DAMP_PBTL (reg 0x02 bit 2) = 1 on U7 before it leaves Hi-Z; the PBTL mixer takes the left I2S frame, so the U7 DSP forms (L+R)/2. No cycle-by-cycle current limit in PBTL.',
    'U25: VOUT = 1.204 V x (1 + 499k/56k) = 11.93 V (PFM: 12.0 V; OVP 12.7-13.6 V). FSW about 494 kHz (RFREQ 301k). ILIM 150k = 7.9 A typ, 6.6 A min in PFM (equation 3). L200 Isat 19.6 A.',
    'COMP: R254 82k, C268 6.8nF, C269 47pF (equations 18-20, fc about 5 kHz, effective Co about 170 uF): calculated only, bench check required. MODE floating = PFM; R256 DNP 0R to GND = forced PWM.',
    'TAS5825M addresses: U6 ADR 0R = 0x4C, U7 ADR 1k = 0x4D. AMP_PDN shared (1k each, 100k pull-down). GPIO0 = FAULTZ (open drain) wired-OR to AMP_FAULT_N, 10k pull-up to 3V3_AUDIO. GPIO1/2 not connected.',
    'DVDD = 3V3_AUDIO. Bootstrap caps are 0.47uF (Table 66). Filter 22uH + 0.68uF per output. No MCLK pin: TAS5825M locks to SCLK. Speaker connectors: pin 1 +, pin 2 -.']
for i, s in enumerate(notes):
    text(s, (NX, NY - 2.54 * i))
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    add.append(f'(hierarchical_label "{nm}" (shape output) (at 215.9 {py} 0) (effects (font (size 1.0 1.0)) (justify right bottom)) (uuid "{U()}"))')
mt = rm_nc(mt, '114.3', '100.33'); mt = rm_text(mt, 'AMP_FAULT_N (reserved)')
add.append(f'(wire (pts (xy 45.72 100.33) (xy 114.3 100.33)) (stroke (width 0) (type default)) (uuid "{U()}"))')
add.append(f'(hierarchical_label "AMP_FAULT_N" (shape input) (at 45.72 100.33 0) (effects (font (size 1.0 1.0)) (justify left bottom)) (uuid "{U()}"))')
assert mt.rstrip().endswith(')')
(ROOT / 'MCU.kicad_sch').write_text(mt.rstrip()[:-1] + '\n'.join(add) + '\n)\n')
print('sheet uuid', SHEET_UUID)
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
